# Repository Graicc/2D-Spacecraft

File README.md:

# Autonomous Hovercraft

Update video: 

A work in progress project to demonstrate control of a 2D "spacecraft" using thrusters.

<!---->

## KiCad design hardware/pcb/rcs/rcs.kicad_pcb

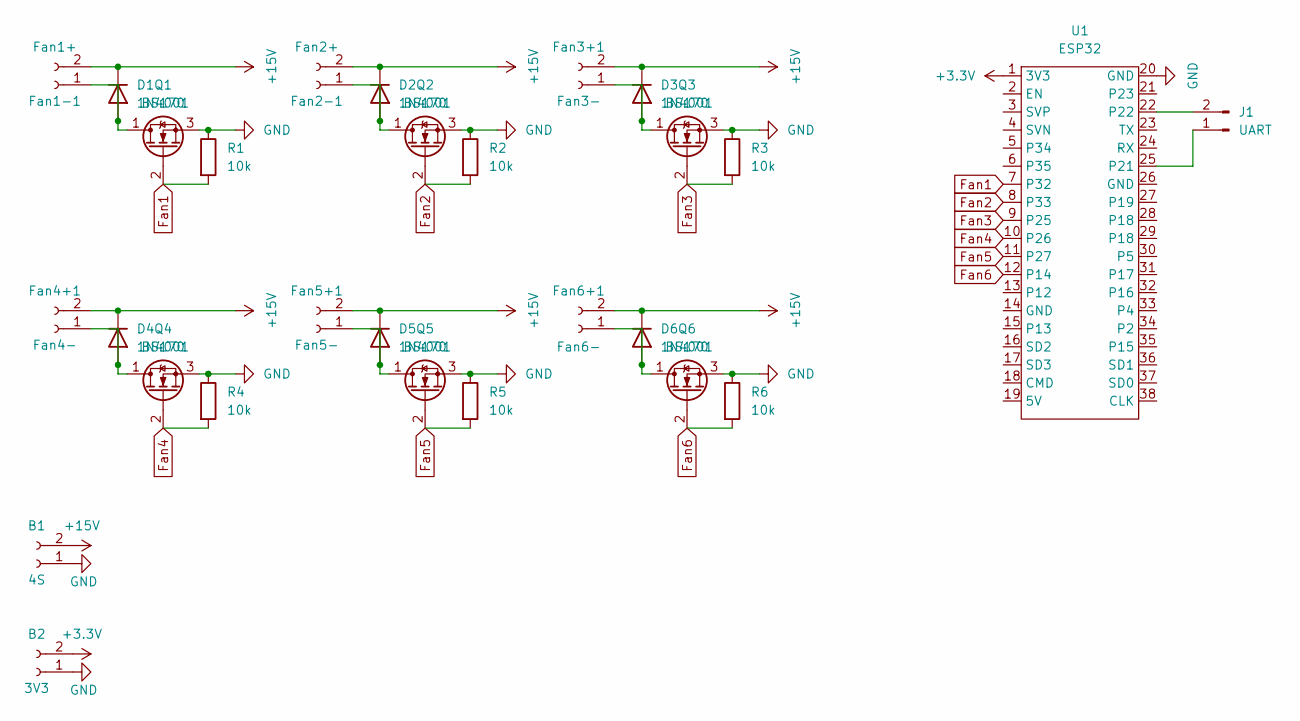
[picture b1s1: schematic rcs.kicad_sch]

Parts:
B1: 4S; PinHeader_1x02_P2.54mm_Vertical
B2: 3V3; PinHeader_1x02_P2.54mm_Vertical
D1, D2, D3, D4, D5, D6: 1N4001; D_DO-41_SOD81_P7.62mm_Horizontal
Fan1-1: Fan1+; PinHeader_1x02_P2.54mm_Vertical
Fan2-1: Fan2+; PinHeader_1x02_P2.54mm_Vertical
Fan3+1: Fan3-; PinHeader_1x02_P2.54mm_Vertical
Fan4+1: Fan4-; PinHeader_1x02_P2.54mm_Vertical
Fan5+1: Fan5-; PinHeader_1x02_P2.54mm_Vertical
Fan6+1: Fan6-; PinHeader_1x02_P2.54mm_Vertical
J1: UART; PinHeader_1x02_P2.54mm_Vertical
Q1, Q2, Q3, Q4, Q5, Q6: BS170; TO-92_Inline_Wide
R1, R2, R3, R4, R5, R6: 10k; R_Axial_DIN0614_L14.3mm_D5.7mm_P20.32mm_Horizontal
U1: ESP32

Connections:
+3.3V: B2.2, U1.1 (3V3)
+15V: B1.2, D1.1 (K), D2.1 (K), D3.1 (K), D4.1 (K), D5.1 (K), D6.1 (K), Fan1-1.2, Fan2-1.2, Fan3+1.2, Fan4+1.2, Fan5+1.2, Fan6+1.2
Fan1: Q1.2 (G), R1.2, U1.7 (P32)
Fan2: Q2.2 (G), R2.2, U1.8 (P33)
Fan3: Q3.2 (G), R3.2, U1.9 (P25)
Fan4: Q4.2 (G), R4.2, U1.10 (P26)
Fan5: Q5.2 (G), R5.2, U1.11 (P27)
Fan6: Q6.2 (G), R6.2, U1.12 (P14)
GND: B1.1, B2.1, Q1.3 (S), Q2.3 (S), Q3.3 (S), Q4.3 (S), Q5.3 (S), Q6.3 (S), R1.1, R2.1, R3.1, R4.1, R5.1, R6.1, U1.20 (GND)
unnamed: D1.2 (A), Fan1-1.1, Q1.1 (D)
unnamed: D2.2 (A), Fan2-1.1, Q2.1 (D)
unnamed: D3.2 (A), Fan3+1.1, Q3.1 (D)
unnamed: D4.2 (A), Fan4+1.1, Q4.1 (D)
unnamed: D5.2 (A), Fan5+1.1, Q5.1 (D)
unnamed: D6.2 (A), Fan6+1.1, Q6.1 (D)
unnamed: J1.1, U1.25 (P21)
unnamed: J1.2, U1.22

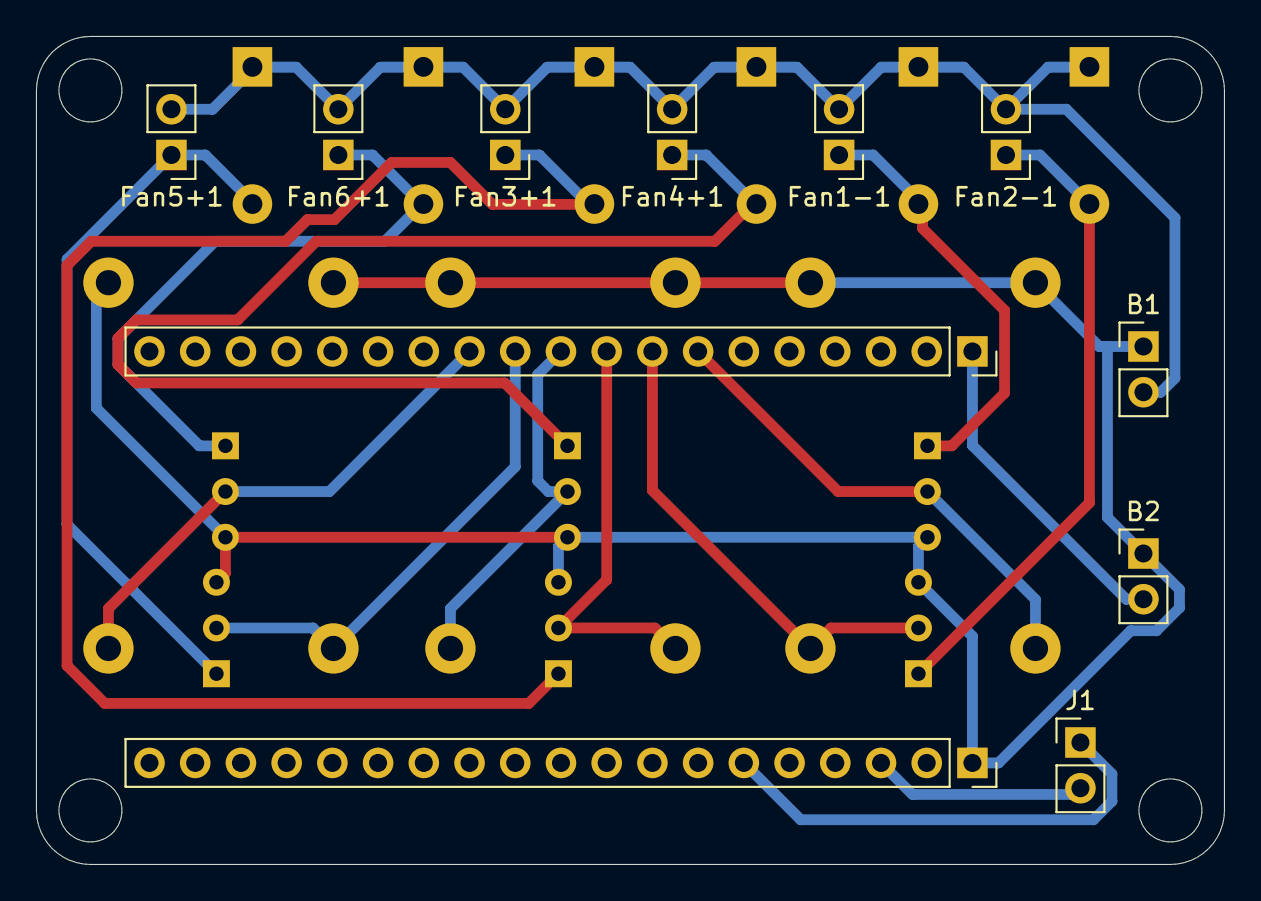
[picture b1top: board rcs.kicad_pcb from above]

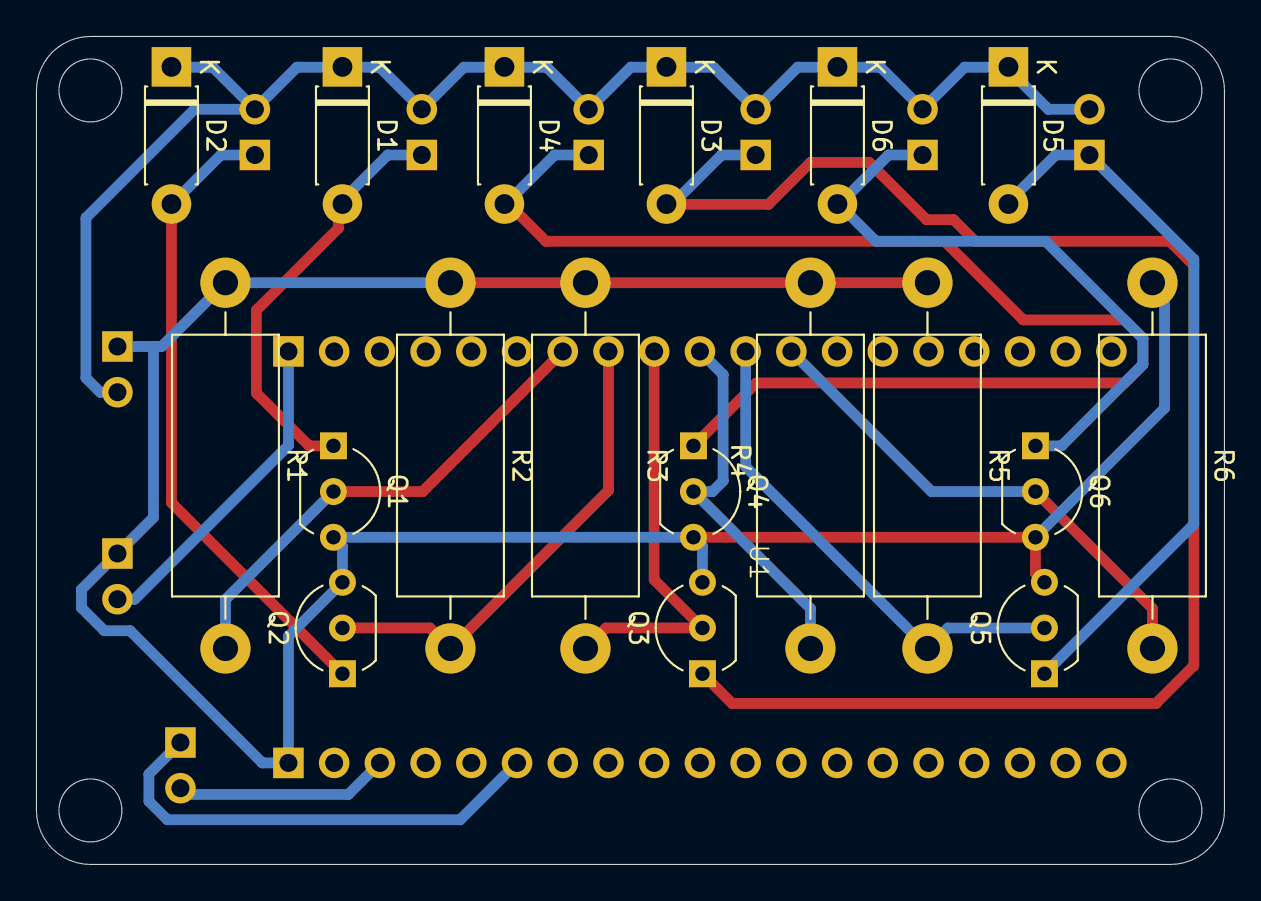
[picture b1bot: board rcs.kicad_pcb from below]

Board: 2 copper layers, 66.0 x 46.0 mm, 28 parts (18 on the bottom side), 17 nets.

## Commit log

2025-02-01 Add web support
2025-02-01 Deploying to gh-pages from @ Graicc/2D-Spacecraft@e610914062ae8ac721fb58cc0fd09d074b67eff6 🚀
2025-02-01 Initial gh-pages commit
2025-02-01 Fix canvas sizing
2025-02-01 Deploying to gh-pages from @ Graicc/2D-Spacecraft@632d1a55d0f43448d7f8758145db6c55e32b2f69 🚀
2025-02-02 Add initial CAD
2025-02-02 Add RCS
2025-02-02 Deploying to gh-pages from @ Graicc/2D-Spacecraft@a91f1f676ab14a320d8bb7235ca569359b58534f 🚀
2025-02-20 Update hole sizing and add propeller
2025-02-24 Add slot for motor wire, add mounting holes for flight controller
2025-02-24 Deploying to gh-pages from @ Graicc/2D-Spacecraft@481478cbb0d5a83712be8304d1989b662d233d8c 🚀
2025-02-24 Add initial PCB
2025-02-26 Add ESP32 dev board schematic and footprint, make draft PCB
2025-03-01 Initialize flight controller firmware
2025-03-01 More compact PCB layout
2025-03-05 Add minimum trace width and screw holes
2025-03-07 Increase trace width to 0.3mm
2025-03-09 Increase trace width to 0.6mm
2025-03-17 Separate simulation code from gui
2025-03-17 Deploying to gh-pages from @ Graicc/2D-Spacecraft@91104592f9edc8b4f199225182d24b4916cf3f5c 🚀
2025-04-14 Fix ESP32 USB port location
2025-04-14 Deploying to gh-pages from @ Graicc/2D-Spacecraft@59c41f432eeeab3af4519e753db5612245a041d6 🚀
2025-04-14 Add fan mount, use assembly
2025-04-22 Send PWM signal to hover
2025-04-22 Add rcs-controller fan testing
2025-04-22 Deploying to gh-pages from @ Graicc/2D-Spacecraft@0bd64077fb173df97a2a6c25e25300faa5ee84a5 🚀
2025-05-07 Update fan mount for height and lock nuts
2025-05-23 Add flyback diodes
2025-05-23 Deploying to gh-pages from @ Graicc/2D-Spacecraft@52e1952738989e40d22b3b22ea3a4aa89c2b48b0 🚀
2025-05-24 Fix flyback diode orientation, round pcb corners
2025-07-19 Add controls model
2025-07-20 Try to get MPC working
2025-09-06 Get logging working on flight controller
2025-09-06 Deploying to gh-pages from @ Graicc/2D-Spacecraft@56ab29cbc006f1d42091aeda5ff3f4ba740ee5e2 🚀
2025-09-06 Read accelerometer values
2025-09-07 Expirement with state estimation from IMU data
2025-09-07 Record IMU data
2025-09-07 Move notebooks to notebooks folder
2025-09-11 Start trajectory planning with casadi
2025-10-03 Move logger to separate file
2025-10-10 Add a bunch of control approaches
2025-10-11 Switch off of workspaces
2025-10-11 Implement async messaging passing library
2025-10-11 Implement RCS controller cmd vel
2025-10-11 Implement flight-controller localization and sending commands
2025-10-11 Deploying to gh-pages from @ Graicc/2D-Spacecraft@9117e67383bd5aeb5b9adc5cd9e76c781f3a9260 🚀
2025-10-11 flight-controller enable motor
2025-10-11 Deploying to gh-pages from @ Graicc/2D-Spacecraft@6334bfd1f496c2e34a5fff639de39c3661e19815 🚀
2025-10-12 Get CasADI working with ipopt!
2025-11-05 Deploying to gh-pages from @ Graicc/2D-Spacecraft@975eb2cb55518f6388fe551e6816cc9d093d825c 🚀
2026-01-02 Add start of infrared tracker
2026-01-02 Deploying to gh-pages from @ Graicc/2D-Spacecraft@a4ae58e7dfde865fa070c756762e5bef36101ea5 🚀
2026-01-02 Add camera calibration
2026-01-02 Add calibration script
2026-01-02 Deploying to gh-pages from @ Graicc/2D-Spacecraft@134ffa670781b4c333544471acdf731ed63abcc2 🚀
2026-01-02 Deploying to gh-pages from @ Graicc/2D-Spacecraft@96056f66417de36b67a1bbbe14b947a10fc353cf 🚀
2026-01-10 Add position detection
2026-01-10 Deploying to gh-pages from @ Graicc/2D-Spacecraft@f15e3d264d482e8206ba257e69654cbed861edc6 🚀
2026-01-24 Add motor brackets for 2 motor design
2026-01-24 Deploying to gh-pages from @ Graicc/2D-Spacecraft@37308e01e7c19508a95c7b89f5b5935b529b600b 🚀
2026-01-28 Port control to Hermite-Simpson Collocation
2026-01-28 Deploying to gh-pages from @ Graicc/2D-Spacecraft@2ea028e0c91e3ccfbe431ae79f8d1238b23c56d7 🚀
2026-01-30 Update dependencies
2026-01-30 Deploying to gh-pages from @ Graicc/2D-Spacecraft@a7fc83aecd9059c3a1c5d02bba53e770a5fe2b8f 🚀
2026-01-30 Switch back to workspace
2026-01-30 Deploying to gh-pages from @ Graicc/2D-Spacecraft@94ef280cc621cc8d60fcbe469ce9fc0127d81241 🚀
2026-01-30 Add notes about flashing
2026-01-31 Get ESP32 wifi ping-pong working
2026-01-31 Deploying to gh-pages from @ Graicc/2D-Spacecraft@02cdb0002e25188e7514304a997f6d8141b6222b 🚀
2026-01-31 Set ESP32 hostname
2026-02-01 Send IMU data to gui
2026-02-01 Deploying to gh-pages from @ Graicc/2D-Spacecraft@97dc663830410595b17ce6172ae8ecab20bdd8ad 🚀
2026-02-05 Add motor control from GUI, add voltage monitor
2026-02-05 Deploying to gh-pages from @ Graicc/2D-Spacecraft@737be48a029bd85253968c3ff957dc4f56cee8b4 🚀
2026-03-26 Update README with update video
2026-03-26 Deploying to gh-pages from @ Graicc/2D-Spacecraft@bf73f6b2b33e5c2e81d2bd50db5443287dd608e6 🚀
